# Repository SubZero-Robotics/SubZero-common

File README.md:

# SubZero-common
SubZero's own library of base components for WPILIB C++ development

# To Add to Repository (Commands in Terminal)

1. `git submodule init`
2. `git submodule add https://github.com/SubZero-Robotics/2025-CommandRobot`
3. `git submodule update`

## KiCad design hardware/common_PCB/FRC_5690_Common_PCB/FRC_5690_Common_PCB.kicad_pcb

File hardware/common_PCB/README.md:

# The ConnectorX

- [The ConnectorX](#the-connectorx)
  - [Overview](#overview)
  - [Features in-depth](#features-in-depth)
    - [LEDs](#leds)
    - [Digital IO](#digital-io)
    - [Analog IO](#analog-io)
    - [Micro SD card](#micro-sd-card)
    - [Configurations](#configurations)
    - [The radio :disappointed: (maybe)](#the-radio-disappointed-maybe)
  - [Commands](#commands)
    - [How they're set up](#how-theyre-set-up)
    - [Command table](#command-table)
  - [The RoboRIO driver](#the-roborio-driver)
  - [Notes about the hardware](#notes-about-the-hardware)

## Overview

## Features in-depth

### LEDs

### Digital IO

### Analog IO

### Micro SD card

### Configurations

### The radio :disappointed: (maybe)

## Commands

### How they're set up

### Command table

ID | Name | R/W | Description
:-: | :-: | :-: | :-:
0 | On | W | Set the current LED port to ON state

## The RoboRIO driver

## Notes about the hardware

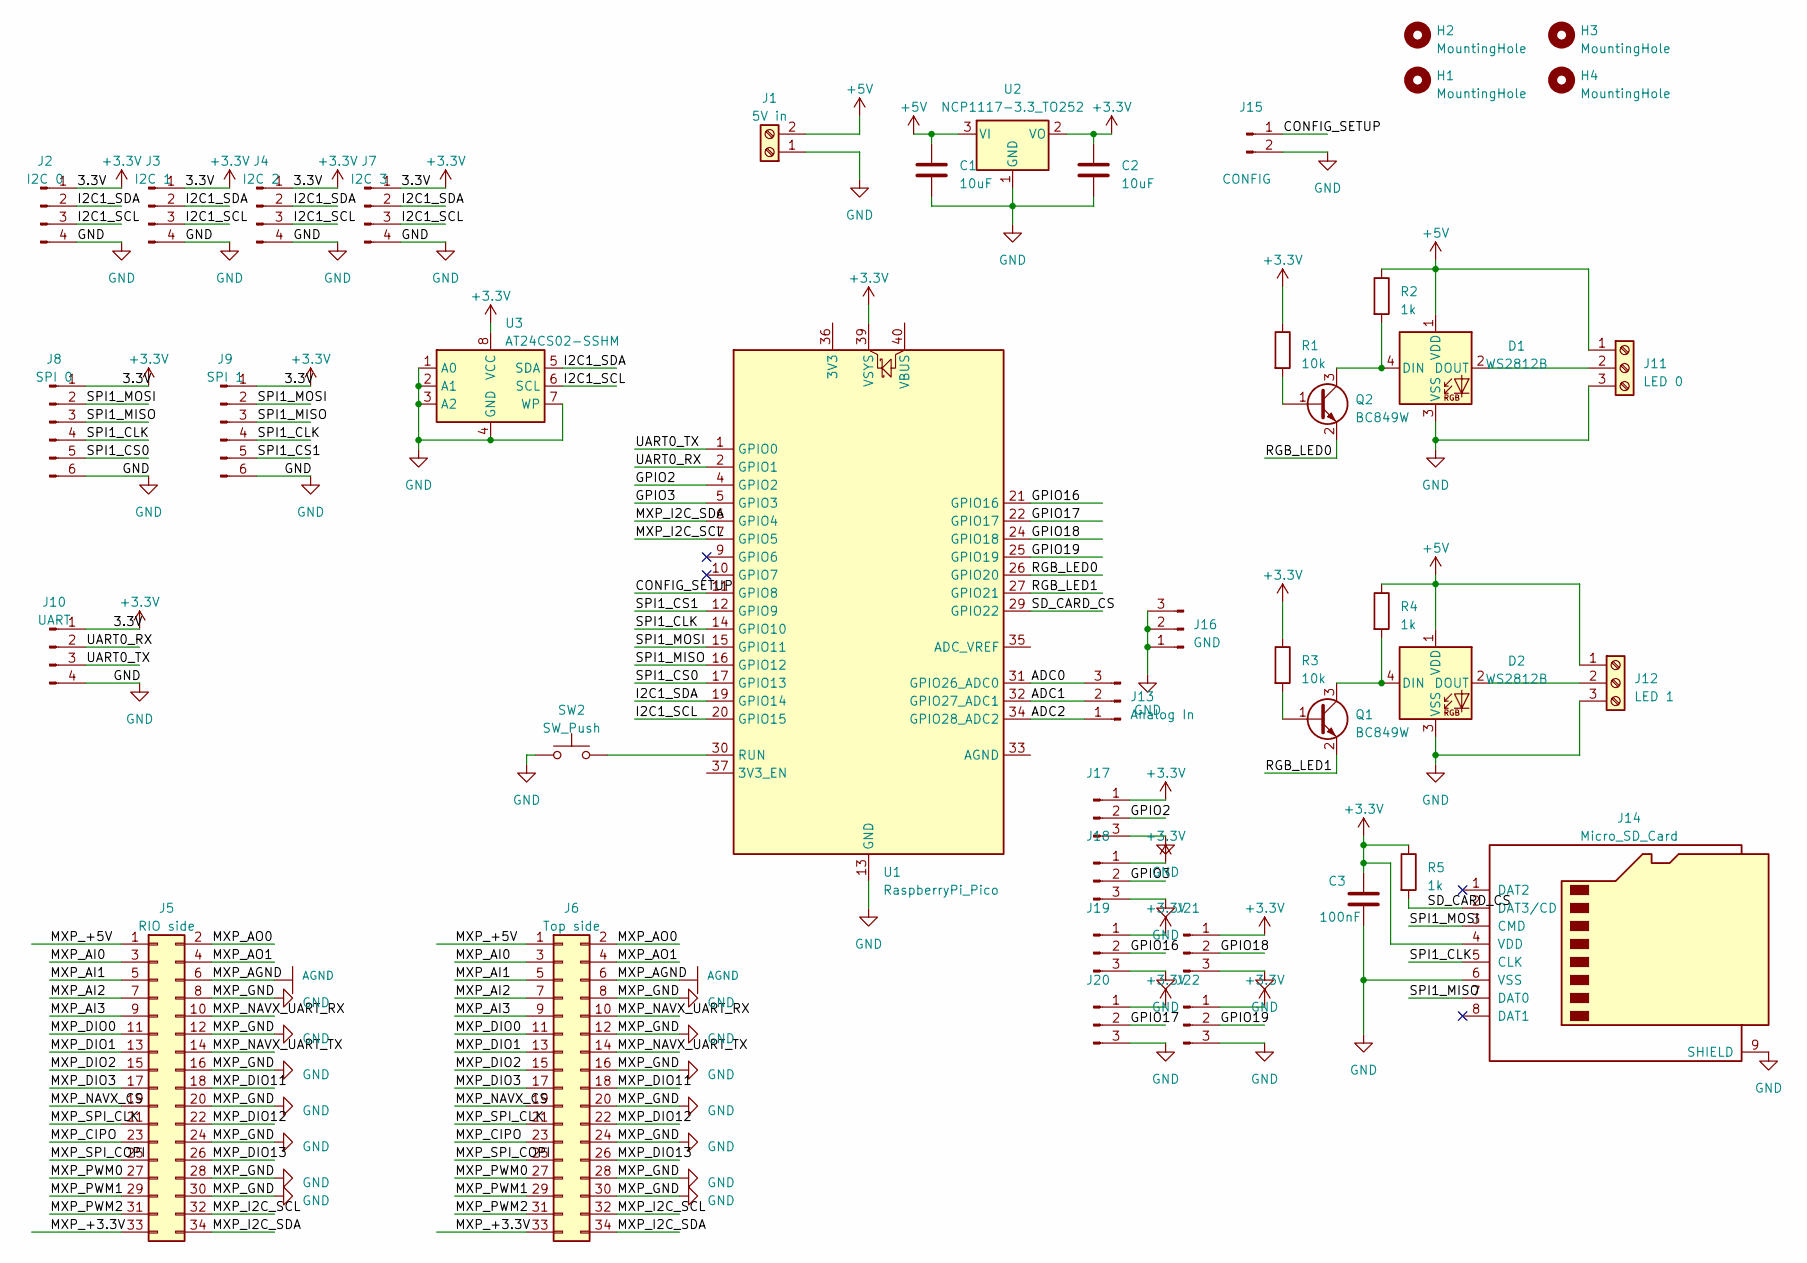
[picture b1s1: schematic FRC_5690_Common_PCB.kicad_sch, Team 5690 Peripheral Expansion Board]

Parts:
C1, C2: 10uF; C_0603_1608Metric
C3: 100nF; C_0603_1608Metric
D1, D2: WS2812B; LED_WS2812B_PLCC4_5.0x5.0mm_P3.2mm
H1, H2, H3, H4: MountingHole; MountingHole_3.2mm_M3_DIN965_Pad
J1: 5V in; TerminalBlock_bornier-2_P5.08mm
J2: I2C 0; PinHeader_1x04_P2.54mm_Vertical
J3: I2C 1; PinHeader_1x04_P2.54mm_Vertical
J4: I2C 2; PinHeader_1x04_P2.54mm_Vertical
J5: RIO side; PinSocket_2x17_P2.54mm_Vertical
J6: Top side; PinHeader_2x17_P2.54mm_Vertical
J7: I2C 3; PinHeader_1x04_P2.54mm_Vertical
J8: SPI 0; PinHeader_1x06_P2.54mm_Vertical
J9: SPI 1; PinHeader_1x06_P2.54mm_Vertical
J10: UART; PinHeader_1x04_P2.54mm_Vertical
J11: LED 0; TerminalBlock_Altech_AK300-3_P5.00mm
J12: LED 1; TerminalBlock_Altech_AK300-3_P5.00mm
J13: Analog In; PinHeader_1x03_P2.54mm_Vertical
J14: Micro_SD_Card; microSD_HC_Hirose_DM3BT-DSF-PEJS
J15: CONFIG; PinHeader_1x02_P2.54mm_Vertical
J16: GND; PinHeader_1x03_P2.54mm_Vertical
J17, J18, J19, J20, J21, J22: Conn_01x03_Pin; PinHeader_1x03_P2.54mm_Vertical
Q1, Q2: BC849W; SOT-323_SC-70
R1, R3: 10k; R_0603_1608Metric
R2, R4, R5: 1k; R_0603_1608Metric
SW2: SW_Push; SW_PUSH_6mm
U1: RaspberryPi_Pico; RaspberryPi_Pico_Common
U2: NCP1117-3.3_TO252; TO-252-2
U3: AT24CS02-SSHM; SOIC-8_3.9x4.9mm_P1.27mm

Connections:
+3.3V: C2.1, C3.1, J2.1, J3.1, J4.1, J7.1, J8.1, J9.1, J10.1, J14.4 (VDD), J17.1, J18.1, J19.1, J20.1, J21.1, J22.1, R1.1, R3.1, R5.1, U1.39 (VSYS), U2.2 (VO), U3.8 (VCC)
+5V: C1.1, D1.1 (VDD), D2.1 (VDD), J1.2, J11.1, J12.1, R2.1, R4.1, U2.3 (VI)
/ADC0: J13.3, U1.31 (GPIO26_ADC0)
/ADC1: J13.2, U1.32 (GPIO27_ADC1)
/ADC2: J13.1, U1.34 (GPIO28_ADC2)
/CONFIG_SETUP: J15.1, U1.11 (GPIO8)
/GPIO2: J17.2, U1.4 (GPIO2)
/GPIO3: J18.2, U1.5 (GPIO3)
/GPIO16: J19.2, U1.21 (GPIO16)
/GPIO17: J20.2, U1.22 (GPIO17)
/GPIO18: J21.2, U1.24 (GPIO18)
/GPIO19: J22.2, U1.25 (GPIO19)
/I2C1_SCL: J2.3, J3.3, J4.3, J7.3, U1.20 (GPIO15), U3.6 (SCL)
/I2C1_SDA: J2.2, J3.2, J4.2, J7.2, U1.19 (GPIO14), U3.5 (SDA)
/MXP_+3.3V: J5.33, J6.33
/MXP_+5V: J5.1, J6.1
/MXP_AI0: J5.3, J6.3
/MXP_AI1: J5.5, J6.5
/MXP_AI2: J5.7, J6.7
/MXP_AI3: J5.9, J6.9
/MXP_AO0: J5.2, J6.2
/MXP_AO1: J5.4, J6.4
/MXP_CIPO: J5.23, J6.23
/MXP_DIO0: J5.11, J6.11
/MXP_DIO1: J5.13, J6.13
/MXP_DIO2: J5.15, J6.15
/MXP_DIO3: J5.17, J6.17
/MXP_DIO11: J5.18, J6.18
/MXP_DIO12: J5.22, J6.22
/MXP_DIO13: J5.26, J6.26
/MXP_I2C_SCL: J5.32, J6.32, U1.7 (GPIO5)
/MXP_I2C_SDA: J5.34, J6.34, U1.6 (GPIO4)
/MXP_NAVX_CS: J5.19, J6.19
/MXP_NAVX_UART_RX: J5.10, J6.10
/MXP_NAVX_UART_TX: J5.14, J6.14
/MXP_PWM0: J5.27, J6.27
/MXP_PWM1: J5.29, J6.29
/MXP_PWM2: J5.31, J6.31
/MXP_SPI_CLK: J5.21, J6.21
/MXP_SPI_COPI: J5.25, J6.25
/RGB_LED0: Q2.2 (E), U1.26 (GPIO20)
/RGB_LED1: Q1.2 (E), U1.27 (GPIO21)
/SD_CARD_CS: J14.2 (DAT3/CD), R5.2, U1.29 (GPIO22)
/SPI1_CLK: J8.4, J9.4, J14.5 (CLK), U1.14 (GPIO10)
/SPI1_CS0: J8.5, U1.17 (GPIO13)
/SPI1_CS1: J9.5, U1.12 (GPIO9)
/SPI1_MISO: J8.3, J9.3, J14.7 (DAT0), U1.16 (GPIO12)
/SPI1_MOSI: J8.2, J9.2, J14.3 (CMD), U1.15 (GPIO11)
/UART0_RX: J10.2, U1.2 (GPIO1)
/UART0_TX: J10.3, U1.1 (GPIO0)
AGND: J5.6, J6.6
GND: C1.2, C2.2, C3.2, D1.3 (VSS), D2.3 (VSS), J1.1, J2.4, J3.4, J4.4, J5.8, J5.12, J5.16, J5.20, J5.24, J5.28, J5.30, J6.8, J6.12, J6.16, J6.20, J6.24, J6.28, J6.30, J7.4, J8.6, J9.6, J10.4, J11.3, J12.3, J14.6 (VSS), J14.9 (SHIELD), J15.2, J16.1, J16.2, J16.3, J17.3, J18.3, J19.3, J20.3, J21.3, J22.3, SW2.1, U1.3 (GND), U1.8 (GND), U1.13 (GND), U1.18 (GND), U1.23 (GND), U1.28 (GND), U1.38 (GND), U2.1 (GND), U3.1 (A0), U3.2 (A1), U3.3 (A2), U3.4 (GND), U3.7 (WP)
unnamed: D1.4 (DIN), Q2.3 (C), R2.2
unnamed: D1.2 (DOUT), J11.2
unnamed: D2.4 (DIN), Q1.3 (C), R4.2
unnamed: D2.2 (DOUT), J12.2
unnamed: Q1.1 (B), R3.2
unnamed: Q2.1 (B), R1.2
unnamed: SW2.2, U1.30 (RUN)

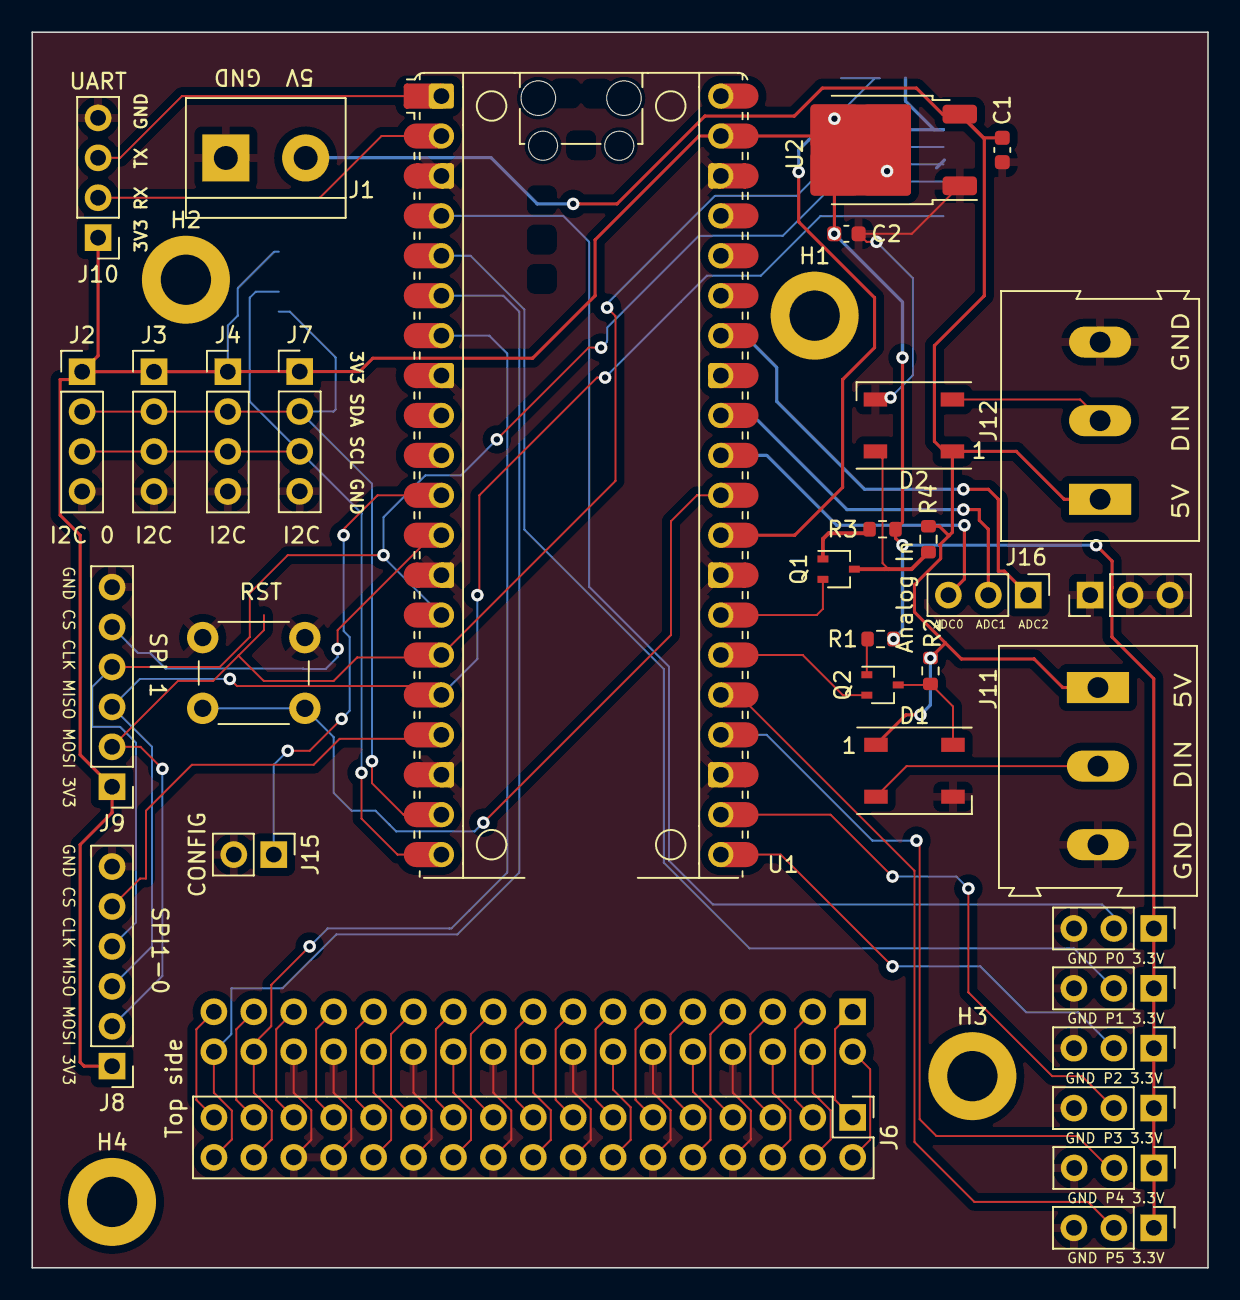
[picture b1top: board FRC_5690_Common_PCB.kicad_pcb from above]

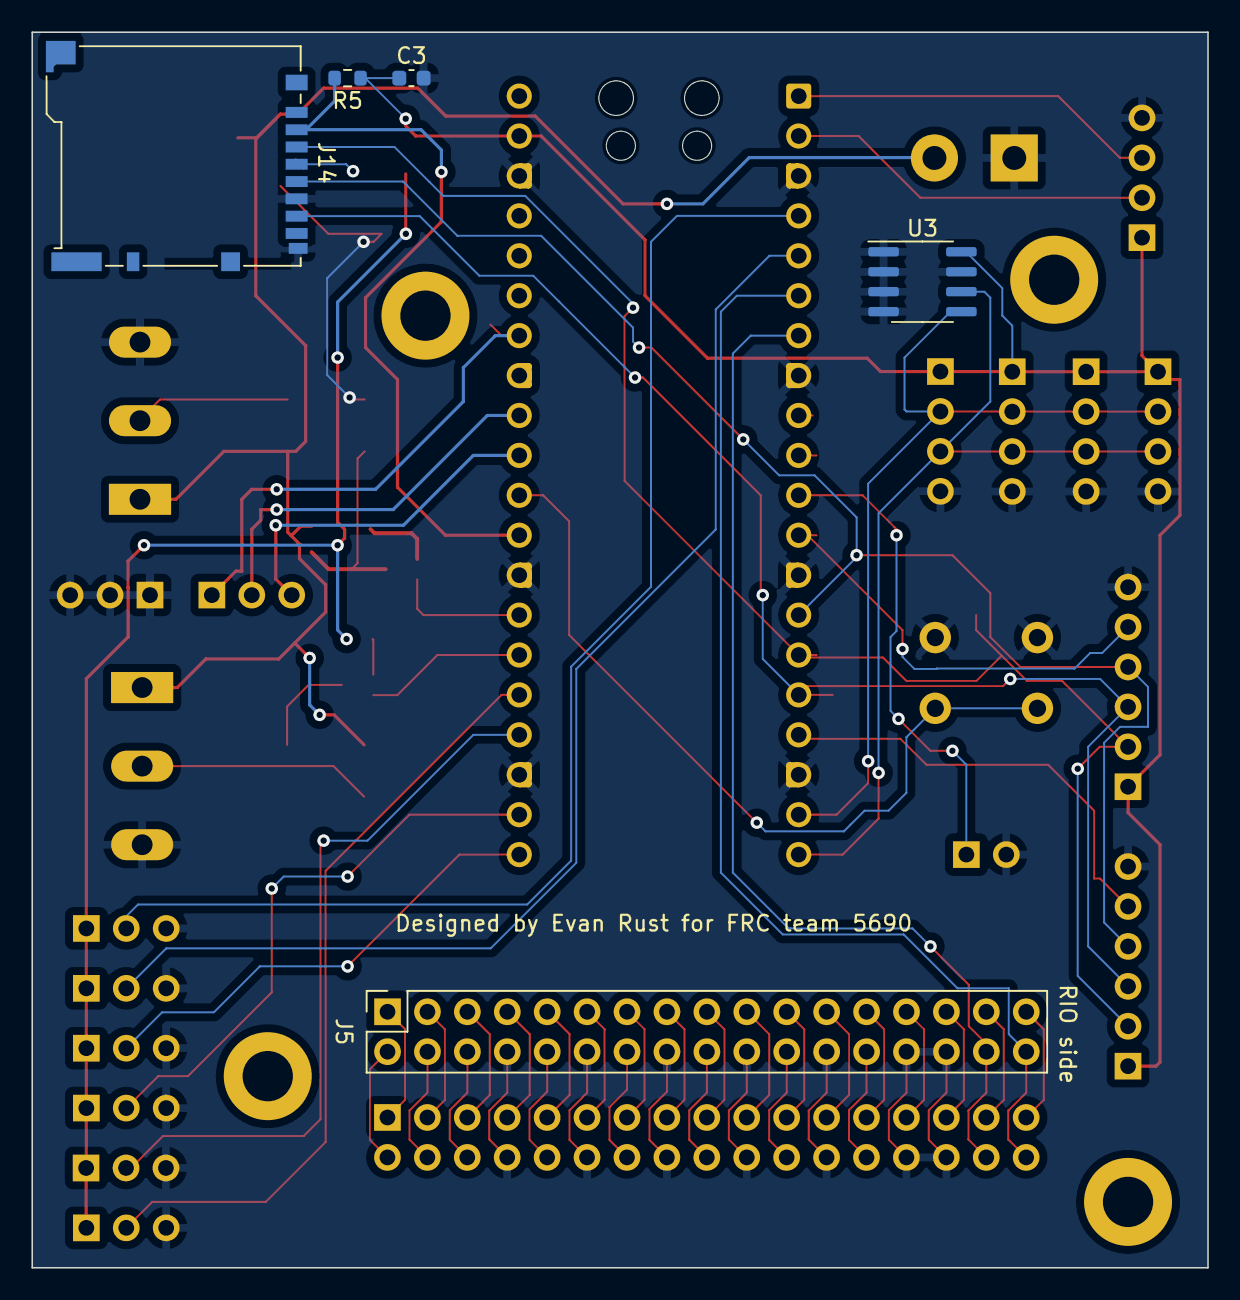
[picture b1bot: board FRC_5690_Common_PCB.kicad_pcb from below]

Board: 2 copper layers, 74.8 x 78.6 mm, 42 parts (5 on the bottom side), 59 nets.

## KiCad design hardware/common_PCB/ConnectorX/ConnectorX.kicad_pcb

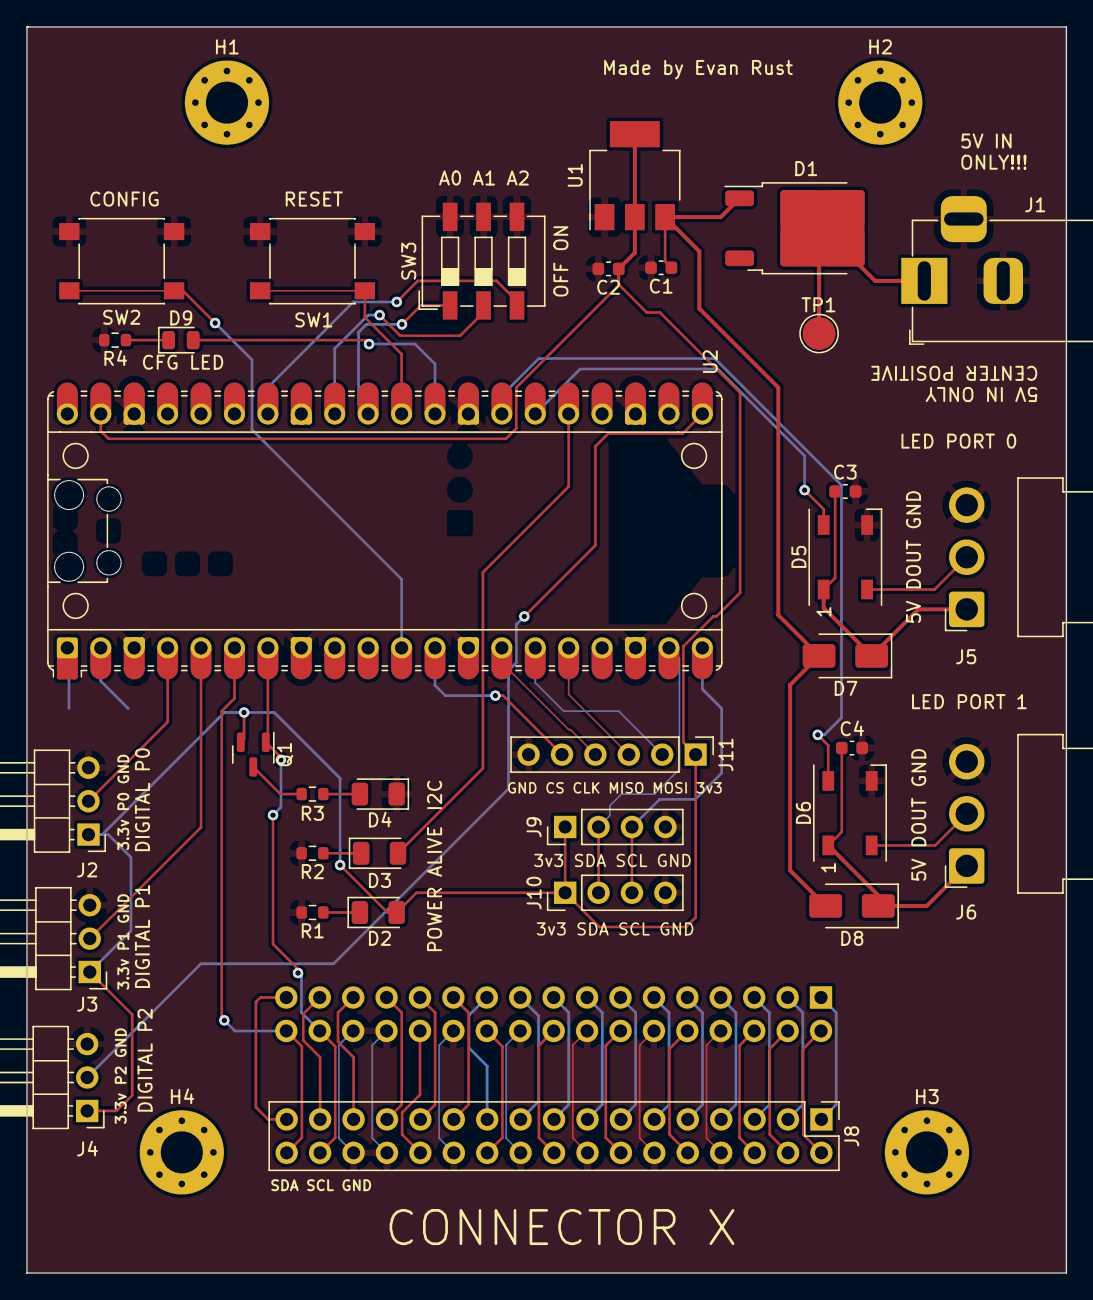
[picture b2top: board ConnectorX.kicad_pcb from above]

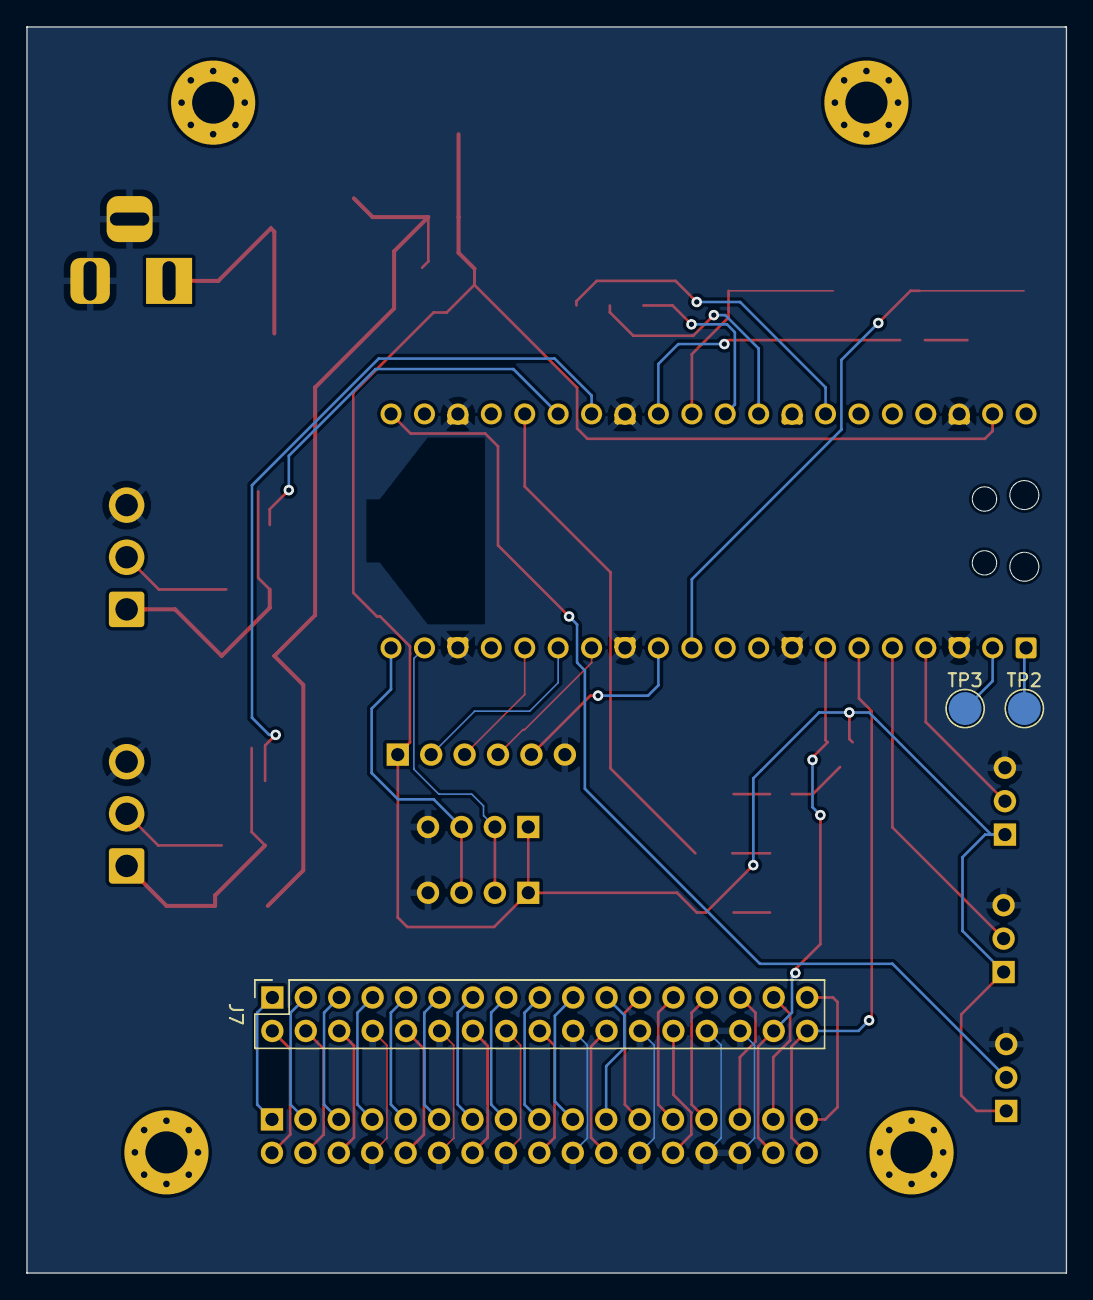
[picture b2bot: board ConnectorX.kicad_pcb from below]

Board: 2 copper layers, 79.0 x 94.7 mm, 41 parts (3 on the bottom side), 60 nets.

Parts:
C1, C2: 10uF; C_0603_1608Metric
C3, C4: 100nF; C_0603_1608Metric
D1: MBRD1060; TO-252-2
D2: PWR; LED_1206_3216Metric
D3: ALV; LED_1206_3216Metric
D4: I2C; LED_1206_3216Metric
D5, D6: WS2812B; LED_WS2812B_PLCC4_5.0x5.0mm_P3.2mm
D7, D8: D_Schottky; D_SMA
D9: CONFIG; LED_0805_2012Metric
H1, H2, H3, H4: MountingHole; MountingHole_3.2mm_M3_Pad_Via
J1: Barrel_Jack_Switch; BarrelJack_Horizontal
J2, J3, J4: Conn_01x03_Socket; PinHeader_1x03_P2.54mm_Horizontal
J5, J6: Conn_01x03_Socket; JST_VH_B3PS-VH_1x03_P3.96mm_Horizontal
J7: RIO side; PinSocket_2x17_P2.54mm_Vertical
J8: Top side; PinHeader_2x17_P2.54mm_Vertical
J9: I2C 0; PinHeader_1x04_P2.54mm_Vertical
J10: I2C 1; PinHeader_1x04_P2.54mm_Vertical
J11: SPI 0; PinHeader_1x06_P2.54mm_Vertical
Q1: IRLML5203TRPBF; SOT-23
R1, R2, R4: 220; R_0603_1608Metric
R3: 470; R_0603_1608Metric
SW1: RST; SW_SPST_PTS645
SW2: CONFIG; SW_SPST_PTS645
SW3: SW_DIP_x03; SW_DIP_SPSTx03_Slide_6.7x9.18mm_W6.73mm_P2.54mm_LowProfile_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
TP1, TP2, TP3: TestPoint; TestPoint_Pad_D2.5mm
U1: NCP1117-3.3_SOT223; SOT-223-3_TabPin2
U2: RaspberryPi_Pico; RaspberryPi_Pico_Common

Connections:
+3.3V: C2.1, D2.2 (A), J2.1, J3.1, J4.1, J9.1, J10.1, J11.1, Q1.2 (S), U1.2 (VO), U2.39 (VSYS)
+5V: C1.1, D1.1 (K), D7.2 (A), D8.2 (A), U1.3 (VI)
/I2C0_SCL: J7.32, J8.32, Q1.1 (G), U2.7 (GPIO5)
/MCU/CFG_LED: D9.2 (A), U2.29 (GPIO22)
/MCU/CGF_SETUP: SW2.2, U2.11 (GPIO8)
/MCU/GPIO2: J2.2, U2.4 (GPIO2)
/MCU/GPIO3: J3.2, U2.5 (GPIO3)
/MCU/GPIO16: J4.2, U2.21 (GPIO16)
/MCU/I2C0_ADDR0: SW3.1, U2.31 (GPIO26_ADC0)
/MCU/I2C0_ADDR1: SW3.2, U2.32 (GPIO27_ADC1)
/MCU/I2C0_ADDR2: SW3.3, U2.34 (GPIO28_ADC2)
/MCU/I2C0_SDA: J7.34, J8.34, U2.6 (GPIO4)
/MCU/I2C1_SCL: J9.3, J10.3, U2.20 (GPIO15)
/MCU/I2C1_SDA: J9.2, J10.2, U2.19 (GPIO14)
/MCU/LED0: D5.4 (DIN), U2.26 (GPIO20)
/MCU/LED1: D6.4 (DIN), U2.27 (GPIO21)
/MCU/RST_SW: SW1.2, U2.30 (RUN)
/MCU/SPI1_CLK: J11.4, U2.14 (GPIO10)
/MCU/SPI1_CS: J11.5, U2.12 (GPIO9)
/MCU/SPI1_MISO: J11.3, U2.16 (GPIO12)
/MCU/SPI1_MOSI: J11.2, U2.15 (GPIO11)
/MCU/UART_RX: TP3.1, U2.2 (GPIO1)
/MCU/UART_TX: TP2.1, U2.1 (GPIO0)
/PICO_ALV: D3.2 (A), U2.25 (GPIO19)
/RIO_connector/MXP_+3.3V: J7.33, J8.33
/RIO_connector/MXP_+5V: J7.1, J8.1
/RIO_connector/MXP_AI0: J7.3, J8.3
/RIO_connector/MXP_AI1: J7.5, J8.5
/RIO_connector/MXP_AI2: J7.7, J8.7
/RIO_connector/MXP_AI3: J7.9, J8.9
/RIO_connector/MXP_AO0: J7.2, J8.2
/RIO_connector/MXP_AO1: J7.4, J8.4
/RIO_connector/MXP_CIPO: J7.23, J8.23
/RIO_connector/MXP_DIO0: J7.11, J8.11
/RIO_connector/MXP_DIO1: J7.13, J8.13
/RIO_connector/MXP_DIO2: J7.15, J8.15
/RIO_connector/MXP_DIO3: J7.17, J8.17
/RIO_connector/MXP_DIO11: J7.18, J8.18
/RIO_connector/MXP_DIO12: J7.22, J8.22
/RIO_connector/MXP_DIO13: J7.26, J8.26
/RIO_connector/MXP_NAVX_CS: J7.19, J8.19
/RIO_connector/MXP_NAVX_UART_RX: J7.10, J8.10
/RIO_connector/MXP_NAVX_UART_TX: J7.14, J8.14
/RIO_connector/MXP_PWM0: J7.27, J8.27
/RIO_connector/MXP_PWM1: J7.29, J8.29
/RIO_connector/MXP_PWM2: J7.31, J8.31
/RIO_connector/MXP_SPI_CLK: J7.21, J8.21
/RIO_connector/MXP_SPI_COPI: J7.25, J8.25
AGND: J7.6, J8.6
GND: C1.2, C2.2, C3.2, C4.2, D4.1 (K), D5.3 (VSS), D6.3 (VSS), J1.2, J1.3, J2.3, J3.3, J4.3, J5.3, J6.3, J7.8, J7.12, J7.16, J7.20, J7.24, J7.28, J7.30, J8.8, J8.12, J8.16, J8.20, J8.24, J8.28, J8.30, J9.4, J10.4, J11.6, R1.2, R2.2, R4.2, SW1.1, SW2.1, SW3.4, SW3.5, SW3.6, U1.1 (GND), U2.3 (GND), U2.8 (GND), U2.13 (GND), U2.18 (GND), U2.23 (GND), U2.28 (GND), U2.38 (GND)
unnamed: D1.2 (A), J1.1, TP1.1
unnamed: D2.1 (K), R1.1
unnamed: D3.1 (K), R2.1
unnamed: D4.2 (A), R3.2
unnamed: D5.2 (DOUT), J5.2
unnamed: C3.1, D5.1 (VDD), D7.1 (K), J5.1
unnamed: D6.2 (DOUT), J6.2
unnamed: C4.1, D6.1 (VDD), D8.1 (K), J6.1
unnamed: D9.1 (K), R4.1
unnamed: Q1.3 (D), R3.1

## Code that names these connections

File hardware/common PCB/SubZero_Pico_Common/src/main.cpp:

#include <Arduino.h>
#include <SD.h>
#include <SPI.h>
#include <Wire.h>

#include <pico/mutex.h>

#include "CommandParser.h"
#include "Commands.h"
#include "Configurator.h"
#include "Constants.h"
#include "PatternRunner.h"

static mutex_t mtx;

// Forward declarations
void receiveEvent(int);
void requestEvent(void);
Adafruit_NeoPixel *getPixels(uint8_t port);
PatternRunner *getPatternRunner(uint8_t port);

static volatile uint8_t receiveBuf[i2cReceiveBufSize];
static volatile bool newData = false;
static volatile bool newDataToParse = false;

static constexpr EEPROMConfiguration eepromConfig = {
    .size = kbits_2, .numDevices = 1, .pageSize = 8, .address = eepromAddr};

static Configuration config;
static Configurator *configurator;
static uint8_t ledPort = 0;

static Adafruit_NeoPixel *pixels0;
static Adafruit_NeoPixel *pixels1;
static PatternRunner *patternRunner0;
static PatternRunner *patternRunner1;

static Command command;

static bool systemOn = true;

void setup() {
  Wire1.setSDA(Pin::I2C::Port1::SDA);
  Wire1.setSCL(Pin::I2C::Port1::SCL);
  Wire1.begin();

  configurator = new Configurator(eepromConfig, &Wire1);

  Serial.begin(115200);
  pinMode(Pin::CONFIG::CONFIG_SETUP, INPUT_PULLUP);
  if (!configurator->checkIfValid() ||
      !digitalRead(Pin::CONFIG::CONFIG_SETUP)) {
    configurator->configSetup();
  }

  config = configurator->readConfig();

  pixels0 = new Adafruit_NeoPixel(config.led0.count, Pin::LED::Dout0,
                                  NEO_GRB + NEO_KHZ800);
  pixels1 = new Adafruit_NeoPixel(config.led1.count, Pin::LED::Dout1,
                                  NEO_GRB + NEO_KHZ800);
  patternRunner0 = new PatternRunner(pixels0, Animation::patterns);
  patternRunner1 = new PatternRunner(pixels1, Animation::patterns);

  // Peripherals
  Wire.setSDA(Pin::I2C::Port0::SDA);
  Wire.setSCL(Pin::I2C::Port0::SCL);
  Wire.onReceive(receiveEvent); // register event
  Wire.onRequest(requestEvent);
  Wire.begin(config.i2c0Addr); // join i2c bus as slave

  SPI1.setTX(Pin::SPI::MOSI);
  SPI1.setRX(Pin::SPI::MISO);
  SPI1.setSCK(Pin::SPI::CLK);
  SPI1.setCS(Pin::SPI::CS0);
  SPI1.begin();

  Serial1.setTX(Pin::UART::Tx);
  Serial1.setRX(Pin::UART::Rx);
  Serial1.begin(uartBaudRate);

  mutex_init(&mtx);

  pinMode(Pin::SPI::CS0, OUTPUT);
  digitalWrite(Pin::SPI::CS0, HIGH);
  pinMode(Pin::SPI::CS1, OUTPUT);
  digitalWrite(Pin::SPI::CS1, HIGH);
  pinMode(Pin::SPI::SdCardCS, OUTPUT);
  digitalWrite(Pin::SPI::SdCardCS, HIGH);
  SD.begin(Pin::SPI::SdCardCS, SPI);

  pinMode(Pin::DIGITALIO::P0, OUTPUT);
  digitalWrite(Pin::DIGITALIO::P0, LOW);
  pinMode(Pin::DIGITALIO::P1, OUTPUT);
  digitalWrite(Pin::DIGITALIO::P1, LOW);
  pinMode(Pin::DIGITALIO::P2, OUTPUT);
  digitalWrite(Pin::DIGITALIO::P2, LOW);
  pinMode(Pin::DIGITALIO::P3, OUTPUT);
  digitalWrite(Pin::DIGITALIO::P3, LOW);
  pinMode(Pin::DIGITALIO::P4, OUTPUT);
  digitalWrite(Pin::DIGITALIO::P4, LOW);
  pinMode(Pin::DIGITALIO::P5, OUTPUT);
  digitalWrite(Pin::DIGITALIO::P5, LOW);

  pinMode(Pin::ANALOGIO::ADC0, INPUT);
  pinMode(Pin::ANALOGIO::ADC1, INPUT);
  pinMode(Pin::ANALOGIO::ADC2, INPUT);

  pixels0->begin();
  pixels0->setBrightness(config.led0.brightness);
  // Initialize all LEDs to black
  Animation::executePatternSetAll(*pixels0, 0, 0, pixels0->numPixels());
  pixels0->show();

  pixels1->begin();
  pixels1->setBrightness(config.led1.brightness);
  // Initialize all LEDs to black
  Animation::executePatternSetAll(*pixels1, 0, 0, pixels1->numPixels());
  pixels1->show();
}

void setup1() {}

Adafruit_NeoPixel *getPixels(uint8_t port) {
  if (port == 0) {
    return pixels0;
  }

  return pixels1;
}

PatternRunner *getPatternRunner(uint8_t port) {
  if (port == 0) {
    return patternRunner0;
  }

  return patternRunner1;
}

void loop() {
  // If there's new data, process it
  if (newData) {
    newData = false;
    uint32_t owner;
    if (mutex_try_enter(&mtx, &owner)) {
      switch (command.commandType) {
      case CommandType::On: {
        // Go back to running the current color and pattern
        patternRunner0->reset();
        patternRunner1->reset();
        systemOn = true;
        break;
      }

      case CommandType::Off: {
        // Set LEDs to black and stop running the pattern
        for (uint8_t port = 0; port < 2; port++) {
          auto pixels = getPixels(ledPort);
          Animation::executePatternSetAll(*pixels, 0, 0, pixels->numPixels());
          pixels->show();
        }
        systemOn = false;
        break;
      }

      case CommandType::Pattern: {
        // To set everything to a certain color, change color then call
        // the 'set all' pattern
        auto runner = getPatternRunner(ledPort);
        uint16_t delay =
            command.commandData.commandPattern.delay == -1
                ? runner->getPattern(command.commandData.commandPattern.pattern)
                      ->changeDelayDefault
                : command.commandData.commandPattern.delay;

        runner->setCurrentPattern(command.commandData.commandPattern.pattern,
                                  command.commandData.commandPattern.oneShot,
                                  delay);
        break;
      }

      case CommandType::ChangeColor: {
        auto runner = getPatternRunner(ledPort);
        auto colors = command.commandData.commandColor;
        runner->setCurrentColor(
            Adafruit_NeoPixel::Color(colors.red, colors.green, colors.blue));
        break;
      }

      case CommandType::SetLedPort: {
        ledPort = command.commandData.commandSetLedPort.port;
        break;
      }

      case CommandType::DigitalSetup: {
        auto cfg = command.commandData.commandDigitalSetup;
        auto pin = Pin::DIGITALIO::digitalIOMap.at(cfg.port);
        pinMode(pin, cfg.mode);
        break;
      }

      case CommandType::DigitalWrite: {
        auto cfg = command.commandData.commandDigitalWrite;
        auto pin = Pin::DIGITALIO::digitalIOMap.at(cfg.port);
        digitalWrite(pin, cfg.value);
        break;
      }

      default:
        break;
      }

      mutex_exit(&mtx);
    }

    Serial.print(F("ON="));
    Serial.println(systemOn);
  }

  if (systemOn) {
    patternRunner0->update();
    patternRunner1->update();
  }
}

void loop1() {
  if (newDataToParse) {
    uint8_t buf[i2cReceiveBufSize];
    // Safely copy our new data
    noInterrupts();
    memcpy(buf, (const void *)receiveBuf, i2cReceiveBufSize);
    interrupts();
    mutex_enter_blocking(&mtx);
    CommandParser::parseCommand(buf, i2cReceiveBufSize, &command);
    mutex_exit(&mtx);

    newDataToParse = false;
    newData = true;
  }
}

void receiveEvent(int howMany) {
  Wire.readBytes((uint8_t *)receiveBuf, howMany);
  newDataToParse = true;
}

void requestEvent() {
  switch (command.commandType) {
  /**
   * @brief Returns uint8_t
   *
   */
  case CommandType::ReadPatternDone: {
    auto runner = getPatternRunner(ledPort);
    Wire.write(runner->patternDone());
    break;
  }

  /**
   * @brief Returns uint16_t
   *
   */
  case CommandType::ReadAnalog: {
    uint16_t value = analogRead(Pin::ANALOGIO::analogIOMap.at(
        command.commandData.commandReadAnalog.port));
    Wire.write((uint8_t *)&value, sizeof(value));
    break;
  }

  /**
   * @brief Returns uint8_t
   *
   */
  case CommandType::DigitalRead: {
    uint8_t value = digitalRead(Pin::DIGITALIO::digitalIOMap.at(
        command.commandData.commandDigitalRead.port));
    Wire.write(value);
    break;
  }

  default:
    // Send back 255 (-1 signed) to indicate bad/no data
    Wire.write(0xff);
  }
}

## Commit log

2023-04-18 Add new folders and files, update some files with existing content
2023-04-25 Add headers and non-robot files
2023-04-25 add common pcb
2023-04-28 migrate to Pico code and add micro SD card slot
2023-04-28 Add bottom silkscreen text to PCB
2023-04-28 use second core
2023-04-28 Add EEPROM
2023-04-29 add configuration for eeprom
2023-04-30 add commands for controlling board
2023-04-30 Fix code style issues with clang_format
2023-04-30 Add brake subsystem framework
2023-04-30 Rename path
2023-04-30 add set config command
2023-05-01 Implement multi axis SetPose
2023-05-04 Implement stop command
2023-05-14 Add packet radio support to ConnectorX
2023-05-15 update driver
2023-05-16 consolidate commands and responses
2023-05-16 implement connectorX driver
2023-05-17 Finish send command
2023-05-18 update pcb
2023-05-18 Fix stop command
2023-05-19 Begin ConnectorX docs
2023-05-23 gerbers
2023-08-11 Basic Library Template (#1)
    * Add new folders and files, update some files with existing content
    * Add headers and non-robot files
    * add common pcb
    * migrate to Pico code and add micro SD card slot
    * Add bottom silkscreen text to PCB
    * use second core
2023-08-13 Fix configurations
2023-08-13 Fix pattern
2023-08-14 Bug/fix-connector-x-initial (#5)
    * Fix configurations
    * Fix pattern
    * Fix code style issues with clang_format
    ---------
2023-08-14 Add Homing, Periodic, and IsMoving Method Implementation
2023-11-15 Create connector X PCB project
2023-11-17 Finalize ConnectorX
2023-11-24 Add submodule
2023-11-24 Fix module drivers
2024-02-05 initial
2024-02-06 Final fixes and bindings
2024-02-17 Add final buttons
2024-04-21 Macro Keypad (#7)
    * initial
    * Fix code style issues with clang_format
    * Final fixes and bindings
    * Add final buttons
    ---------
2024-04-21 add new utils
2024-05-13 Cleanup and begin bringing over common utilities from 2024 robot
2024-05-17 fix modifyable chooser
2024-05-20 Copy generic classes
2024-05-20 make build
2024-05-20 break everything
2024-05-21 oops
2024-05-21 fix inclusions
2024-05-21 comments for 1/3
2024-05-21 through linear single axis
2024-05-21 Finish comments
2024-05-21 doxygen
2024-05-21 gitignore
2024-05-21 gh action
2024-05-21 update doxygen workflow name
2024-05-21 add pr to doxygen action
2024-05-21 update task version
2024-05-21 output dir
2024-05-21 keep html folder
2024-05-21 change gen location
2024-05-21 bump
2024-05-21 working dir
2024-05-21 only look in certain folder
2024-05-21 use subzero ns
2024-05-21 Add EmptyCommand, run formatter
2024-05-21 Use EmptyCommand in autos
2024-05-22 switch to doxygen-awesome css
2024-05-22 auto-deploy pages
2024-05-22 update doxygen workflow
2024-05-22 use token
2024-05-22 deploy with different task
2024-05-22 update dest
2024-05-22 uh oh
2024-05-22 Initial gh-pages commit
2024-05-22 Deploying to gh-pages from @ SubZero-Robotics/SubZero-common@a37a889d0b74bf9006a5d2e93ca1ff31ec24fa40 🚀
2024-05-22 fix doxyfile
2024-05-22 Deploying to gh-pages from @ SubZero-Robotics/SubZero-common@afe3986f9b84a63011d50a017530eacb1d6bc079 🚀
2024-05-22 undo?
2024-05-22 Deploying to gh-pages from @ SubZero-Robotics/SubZero-common@87e93bc184066e263f48d52c2efa78655662138f 🚀
2024-05-22 Deploying to gh-pages from @ SubZero-Robotics/SubZero-common@7feab58b05bd3b3e4155999b622b9c82d5b33880 🚀
2024-05-22 recurse
2024-05-22 Deploying to gh-pages from @ SubZero-Robotics/SubZero-common@8515c9a270156dbb04546010a8eb7dd5a31d5bde 🚀
2024-05-23 Deploying to gh-pages from @ SubZero-Robotics/SubZero-common@14af21a34b12acd9800a5514841a76a31f568b53 🚀
2024-05-23 Move 2024 Season into Common (#9)
    * Cleanup and begin bringing over common utilities from 2024 robot
    * fix modifyable chooser
    * Copy generic classes
    * make build
    * break everything
    * oops
2024-05-23 Deploying to gh-pages from @ SubZero-Robotics/SubZero-common@86b0b154419bb718c54bdd3ee585dabdf4818b5a 🚀
2024-05-24 switch over 1/3
2024-05-24 BASE SINGLE AXIS
2024-05-24 Deploying to gh-pages from @ SubZero-Robotics/SubZero-common@55b1a992870295cada3d6c15d66f2c8490ea49f7 🚀
2024-05-24 Place template implementations into cpp files (#10)
    * switch over 1/3
    * BASE SINGLE AXIS
    * Fix code style issues with clang_format
    ---------
2024-05-24 Deploying to gh-pages from @ SubZero-Robotics/SubZero-common@739898a17c5f7e65e2a68bbfa46608dd2520c8d3 🚀
2024-05-24 small fix
2024-05-24 Deploying to gh-pages from @ SubZero-Robotics/SubZero-common@073fd2e2d2a98352adf4b24f4b24a5cb9520bf02 🚀
2024-06-13 Deploying to gh-pages from @ SubZero-Robotics/SubZero-common@40bbbd332b9dedcf166411f19c6a43a230ad97d5 🚀
2024-06-22 sim pid motor controller
2024-06-22 Deploying to gh-pages from @ SubZero-Robotics/SubZero-common@3b12aa63f443931c06d2e732928d3b505f261d2d 🚀
2024-06-22 Simulatable Single Axis Subsystems (#11)
    * sim pid motor controller
    * Fix code style issues with clang_format
    ---------
2024-06-22 Deploying to gh-pages from @ SubZero-Robotics/SubZero-common@d08352f59d4b3955bb0fce94a173ad9c2a210db3 🚀
2024-06-22 air quality project
2024-06-22 use merge strategy
2024-06-28 rotate display in software
2024-07-15 add 3d positioning
2024-07-28 Implement the SwerveUtils header
2024-07-28 Deploying to gh-pages from @ SubZero-Robotics/SubZero-common@53de6f575b100358f3bbe8544fe2522c6fdcffa3 🚀
2024-07-28 Fix parameter names and add early returns
2024-07-28 Deploying to gh-pages from @ SubZero-Robotics/SubZero-common@dde4875a91df612c47626c592b389ceab1a19765 🚀
2024-07-28 Implement the SwerveUtils header (#13)
    * Implement the SwerveUtils header
    * Fix code style issues with clang_format
    * Fix parameter names and add early returns
    * Fix code style issues with clang_format
    ---------
2024-07-28 Deploying to gh-pages from @ SubZero-Robotics/SubZero-common@4c7c4c093292704d97a775358a5cbbccb991c06a 🚀
2025-01-09 changes needed to get building in 2025 (minus changes to singleaxis)
2025-01-17 changes needed to get building in 2025 (minus changes to singleaxis) (#15)
2025-01-17 Deploying to gh-pages from @ SubZero-Robotics/SubZero-common@c1c8938c7b3a1376d9743db89e25336d386b0036 🚀
2025-01-20 changes needed to get building in 2025 (minus changes to singleaxis) … (#17)
    * changes needed to get building in 2025 (minus changes to singleaxis) (#15)
    * Fix code style issues with clang_format
    ---------
2025-01-20 Deploying to gh-pages from @ SubZero-Robotics/SubZero-common@e6a80db36996ba139a6a4907eb0fcda08c81b074 🚀
2025-01-31 Try to get rev 2025 fixing (doesn't build)
2025-01-31 Comment out errors; code builds doesn't work
2025-02-01 Use rev pid config (builds)
2025-02-01 Fix `SetEncoderConversionFactor()` and `SetAbsoluteEncoderConversionFactor()`
2025-02-01 Deploying to gh-pages from @ SubZero-Robotics/SubZero-common@576e7722215e6e9b55277f5ec5587ba434da262a 🚀
2025-02-01 Remove autofactory method implementations in header file
2025-02-01 Deploying to gh-pages from @ SubZero-Robotics/SubZero-common@6a34c1e4032ee1e4f289d2138b75a962a5acbe5e 🚀
2025-02-01 Add template type for pid config in `PidMotorControllerTuner`
2025-02-01 Deploying to gh-pages from @ SubZero-Robotics/SubZero-common@ddcde5dc71805a3fd7952bc93ab17993e340aa4a 🚀
2025-02-03 Remove solved TODOs
2025-02-03 Deploying to gh-pages from @ SubZero-Robotics/SubZero-common@35a11fbddc126775ba8aeb04607109b59649632a 🚀
2025-02-03 Remove `TODO` in PID
2025-02-03 Deploying to gh-pages from @ SubZero-Robotics/SubZero-common@14cb4a981facfd84cd685b436efbc01f47e1a519 🚀
2025-02-04 Add default behavior to pit settings object
2025-02-04 Deploying to gh-pages from @ SubZero-Robotics/SubZero-common@09c6f6d5840989bfa6125b7be86df019275f9b12 🚀
2025-02-04 `ISingleAxisSubsystem` fixes (#22)
    * Try to get rev 2025 fixing (doesn't build)
    * Comment out errors; code builds doesn't work
    * Use rev pid config (builds)
    * Fix `SetEncoderConversionFactor()` and `SetAbsoluteEncoderConversionFactor()`
    * Fix code style issues with clang_format
    * Remove autofactory method implementations in header file
2025-02-04 Deploying to gh-pages from @ SubZero-Robotics/SubZero-common@3c01c9ce669d96bec7d854ee44118f6a3bac9ca0 🚀
2025-02-07 Add new `RevPidMotorController` class
2025-02-08 Added instructions to add submodule
2025-02-13 Deploying to gh-pages from @ SubZero-Robotics/SubZero-common@fa49423c875a12f27b50c0cfc58c7cbd5a5ebbc6 🚀
2025-02-15 Add logging and update brake mode with tuner
2025-02-15 Deploying to gh-pages from @ SubZero-Robotics/SubZero-common@2c8842ec2e0f67eb94ee8e9e77c01d004969d255 🚀
2025-02-15 Fix PID Tuner for 2025 (#23)
    * Add logging and update brake mode with tuner
    * Fix code style issues with clang_format
    ---------
2025-02-15 Deploying to gh-pages from @ SubZero-Robotics/SubZero-common@f890b47ca056c55762f1d6c4a07655addf0066cb 🚀
